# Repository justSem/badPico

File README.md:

# badPico!
An [RP2040](https://www.raspberrypi.com/products/rp2040/) mini-sized BadUSB clone

_Size: 19x39mm_

This tiny (19x34mm) device is just a common "Rubber Ducky" clone.

Without software this is just an RP2040-on-a-stick ;)

# Usage
A good starting point for this board is the [BadPico Repository](https://github.com/EvgeniGenchev/BadPico) by @EvgeniGenchev.

The board in general works identical to a Raspberry [Pi Pico](https://www.raspberrypi.com/products/raspberry-pi-pico/) and can be programmed as such.
However, due to the intended use-case the I/O pins are not available for usage with the exception of those listed below.

# PinOuts

| Designator	| GPIO  |  Type 	| Description 							|
| ------------- | ----- | ------------- | ------------------------------------------------------------- |
|  D4		| 25	| LED		| Status LED  							|
|  D3		| 24	| LED		| User-programmable LED 					|
| SW1		| 0	| Switch	| User-programmable switch. I use it as an 'arming' switch 	| 

# Bill of Materials (BoM)
| Name	| Designator	| Footprint	| Manufacturer		| Man. Part No.			|
| ----- | ------------- | ------------- | --------------------- | ----------------------------- |
| 27pF	| C15,C16	| C0402		| FH			| 0402CG270J500NT		|
| 100nF | C1-C9,C12	| C0402		| Yaego			| CC0402KRX7R7BB104		|
| 1uF	| C10,C11	| C0402		| Samsung		| CL05A105KQ5NNNC		|
| 10uF	| C13,C14	| C0603		| Samsung		| CL10A106MP8NNNC		| 
| Y	| Y1		| 5032		| Abracon		| ABMM2-12.000MHZ-E2-T 		|
| 24.7R	| R3,R4		| R0402		| FH			| RC-02W27R4FT 			|
| 330R	| R5		| R0402		| FOJAN			| FRC1206J331			|
| 1k	| R7,R9,R10,R11	| R0402		| Walsin		| MR04X102			|
| 100k	| R8		| R0402		| FH			| RS-03K104JT			|
| Flash	| U1		| WSON-8	| Winbond Elec		| W25Q128JVPIQ			|
| LDO	| U2		| TSOT-23-5	| Maxlinear		| SPX3819M5-L-3-3		|
| RP2040 | U3		| QFN-56	| Raspberry Pi		| RP2040			|
| FET	| Q1		| SOT-24	| Vishay		| Si2319CDS			|
| Diode	| D2		| SOD_123F	| Shandong		| 1N4002W			|
| LEDs	| D3,D4		| D0402		| Everlight		| 17-21/BHC-XL2M2TY/3T		|
| Fuse	| F1		| F0805		| LittelFuse		| 0805L050WR			|
| Bead	| FB1		| F0402		| Chillsin		| BBSY00100505101Y00		|
| USB	| J1		| Custom	| XKB Connectivity	| U217-041N-4BV81 		|
| SWT	| SW2,SW3	| Custom	| ALPS			| SKRKAEE020			|
| SWF	| SW1		| Custom	| Shou Han		| SK12D07VG4			|

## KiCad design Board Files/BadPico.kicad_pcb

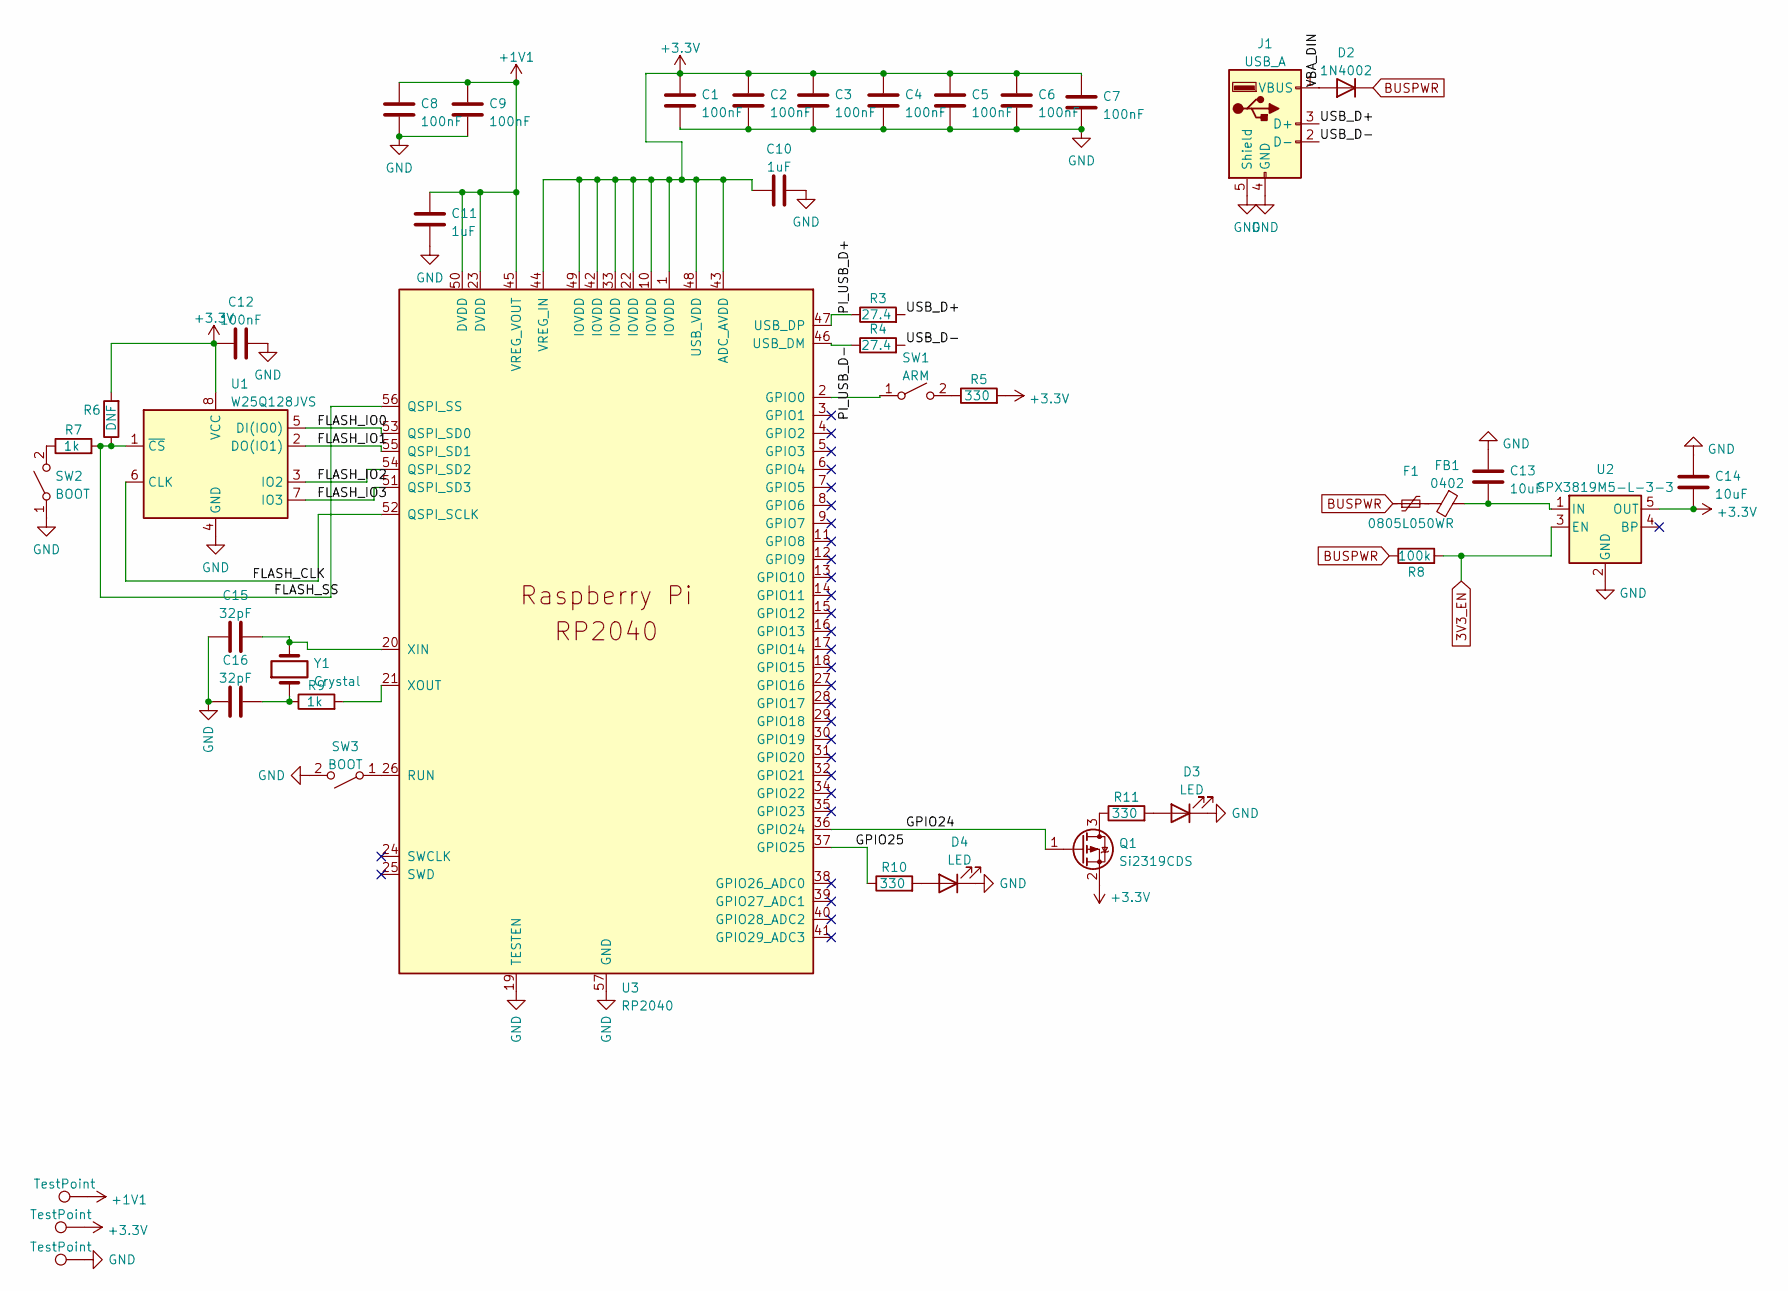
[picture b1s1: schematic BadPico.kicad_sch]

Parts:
C1, C2, C3, C4, C5, C6, C7, C8, C9, C12: 100nF; C_0402_1005Metric
C10, C11: 1uF; C_0402_1005Metric
C13, C14: 10uF; C_0603_1608Metric
C15, C16: 32pF; C_0402_1005Metric
D2: 1N4002; D_SOD-123F
D3, D4: LED; LED_0402_1005Metric
F1: 0805L050WR; Fuse_0805_2012Metric
FB1: 0402; R_0402_1005Metric
J1: USB_A; Male_Type-A-XKB-U217-041N-4BV81
Q1: Si2319CDS; SOT-23
R3, R4: 27.4; R_0402_1005Metric
R5, R10, R11: 330; R_0402_1005Metric
R6: DNF; R_0402_1005Metric
R7, R9: 1k; R_0402_1005Metric
R8: 100k; R_0402_1005Metric
SW1: ARM; SW_DPDT_SK12D07VG4
SW2, SW3: BOOT; SW_SPST_ALPS_SKRKAEE020
TP3, TP4, TP5: TestPoint; TestPoint_Pad_2.0x2.0mm
U1: W25Q128JVS; WSON-8-1EP_6x5mm_P1.27mm_EP3.4x4mm
U2: SPX3819M5-L-3-3; SOT-23-5
U3: RP2040; RP2040-QFN-56
Y1: Crystal; Crystal_SMD_5032-2Pin_5.0x3.2mm

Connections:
3V3_EN: R8.2, U2.3 (EN)
+1V1: C8.1, C9.1, C11.2, TP3.1, U3.23 (DVDD), U3.45 (VREG_VOUT), U3.50 (DVDD)
+3V3: C1.1, C2.1, C3.1, C4.1, C5.1, C6.1, C7.1, C10.1, C12.1, C14.1, Q1.2 (S), R5.2, R6.2, TP4.1, U1.8 (VCC), U2.5 (OUT), U3.1 (IOVDD), U3.10 (IOVDD), U3.22 (IOVDD), U3.33 (IOVDD), U3.42 (IOVDD), U3.43 (ADC_AVDD), U3.44 (VREG_IN), U3.48 (USB_VDD), U3.49 (IOVDD)
/FLASH_CLK: U1.6 (CLK), U3.52 (QSPI_SCLK)
/FLASH_IO0: U1.5 (DI(IO0)), U3.53 (QSPI_SD0)
/FLASH_IO1: U1.2 (DO(IO1)), U3.55 (QSPI_SD1)
/FLASH_IO2: U1.3 (IO2), U3.54 (QSPI_SD2)
/FLASH_IO3: U1.7 (IO3), U3.51 (QSPI_SD3)
/FLASH_SS: R6.1, R7.2, U1.1 (~CS), U3.56 (QSPI_SS)
/GPIO24: Q1.1 (G), U3.36 (GPIO24)
/GPIO25: R10.1, U3.37 (GPIO25)
/PI_USB_D+: R3.1, U3.47 (USB_DP)
/PI_USB_D-: R4.1, U3.46 (USB_DM)
/USB_D+: J1.3 (D+), R3.2
/USB_D-: J1.2 (D-), R4.2
/VBA_DIN: D2.2 (A), J1.1 (VBUS)
BUSPWR: D2.1 (K), F1.1, R8.1
GND: C1.2, C2.2, C3.2, C4.2, C5.2, C6.2, C7.2, C8.2, C9.2, C10.2, C11.1, C12.2, C13.2, C14.2, C15.2, C16.2, D3.1 (K), D4.1 (K), J1.4 (GND), J1.5 (Shield), SW2.1 (A), SW3.2 (B), TP5.1, U1.4 (GND), U1.9, U2.2 (GND), U3.19 (TESTEN), U3.57 (GND)
unnamed: C13.1, FB1.1, U2.1 (IN)
unnamed: C15.1, U3.20 (XIN), Y1.2
unnamed: C16.1, R9.1, Y1.1
unnamed: D3.2 (A), R11.2
unnamed: D4.2 (A), R10.2
unnamed: F1.2, FB1.2
unnamed: Q1.3 (D), R11.1
unnamed: R7.1, SW2.2 (B)
unnamed: R9.2, U3.21 (XOUT)
unnamed: R5.1, SW1.2 (B)
unnamed: SW3.1 (A), U3.26 (RUN)
unnamed: SW1.1 (A), U3.2 (GPIO0)

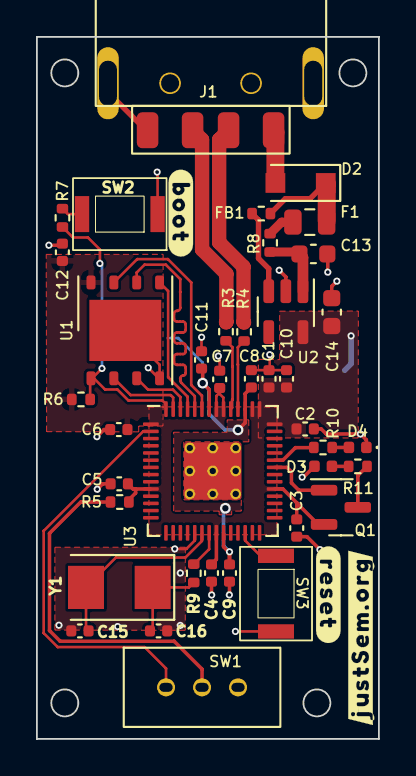
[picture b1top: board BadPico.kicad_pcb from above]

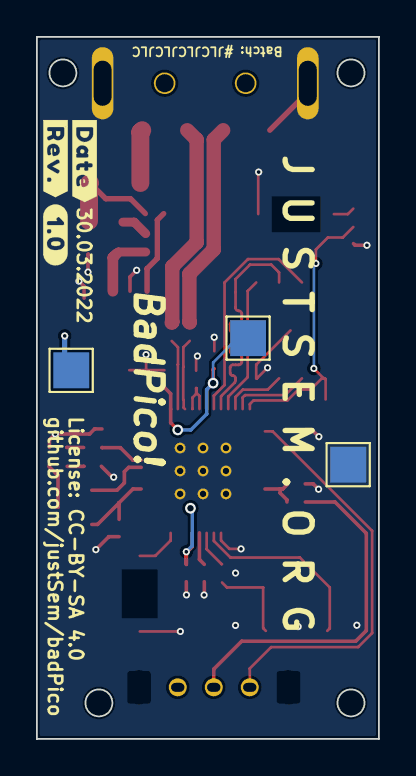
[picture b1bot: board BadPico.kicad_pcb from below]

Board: 2 copper layers, 19.0 x 39.0 mm, 42 parts (3 on the bottom side), 30 nets.

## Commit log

2022-04-01 Rev 1.0
2022-04-01 Added board images

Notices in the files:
Board Files/BadPico.kicad_pcb:
License: CC-BY-SA 4.0
